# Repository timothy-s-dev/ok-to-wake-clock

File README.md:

# OK-to-Wake Clock - ESP32 Multi-Function Clock

This project provides code for a digital OK-to-Wake clock using an ESP32 with
multiple input and output components. The clock includes rotary encoder input
(w/ switch), RGB LED state indicator, alphanumeric display, and an RTC with
battery backup so the time is not lost when power is.

A schedule can be set for each day of the week, with the following time windows:

* Wind Down (Blue)
* Sleep (Red)
* Quiet (Yellow)
* Wake (White)

Depending on which window the current time falls in for the current day's
schedule the RGB LED will change colors.

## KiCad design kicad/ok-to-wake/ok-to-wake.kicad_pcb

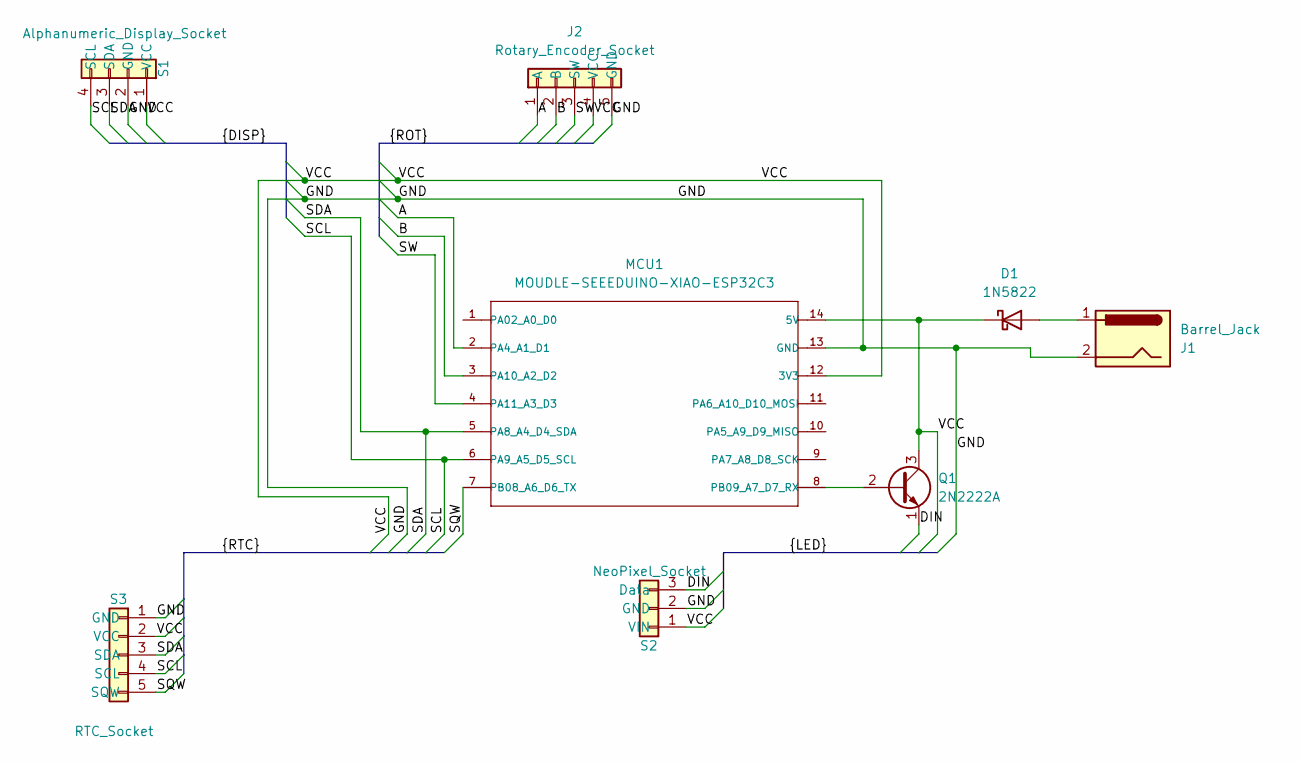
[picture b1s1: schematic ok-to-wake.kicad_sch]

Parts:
D1: 1N5822; D_DO-201AD_P15.24mm_Horizontal
J1: Barrel_Jack; JST_XH_B2B-XH-A_1x02_P2.50mm_Vertical
J2: Rotary_Encoder_Socket; JST_XH_B5B-XH-AM_1x05_P2.50mm_Vertical
MCU1: MOUDLE-SEEEDUINO-XIAO-ESP32C3; MCU_Seeed_ESP32C3
Q1: 2N2222A; TO-92
S1: Alphanumeric_Display_Socket; JST_XH_B4B-XH-AM_1x04_P2.50mm_Vertical
S2: NeoPixel_Socket; JST_XH_B3B-XH-AM_1x03_P2.50mm_Vertical
S3: RTC_Socket; PinHeader_1x05_P2.54mm_Vertical

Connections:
/A: J2.1 (A), MCU1.2 (PA4_A1_D1)
/B: J2.2 (B), MCU1.3 (PA10_A2_D2)
/DIN: Q1.1 (E), S2.3 (Data)
/GND: J1.2, J2.5 (GND), MCU1.13 (GND), S1.2 (GND), S2.2 (GND), S3.1 (GND)
/SCL: MCU1.6 (PA9_A5_D5_SCL), S1.4 (SCL), S3.4 (SCL)
/SDA: MCU1.5 (PA8_A4_D4_SDA), S1.3 (SDA), S3.3 (SDA)
/SQW: MCU1.7 (PB08_A6_D6_TX), S3.5 (SQW)
/SW: J2.3 (SW), MCU1.4 (PA11_A3_D3)
/VCC: D1.1 (K), J2.4 (VCC), MCU1.12 (3V3), MCU1.14 (5V), Q1.3 (C), S1.1 (VCC), S2.1 (VIN), S3.2 (VCC)
unnamed: D1.2 (A), J1.1
unnamed: MCU1.8 (PB09_A7_D7_RX), Q1.2 (B)

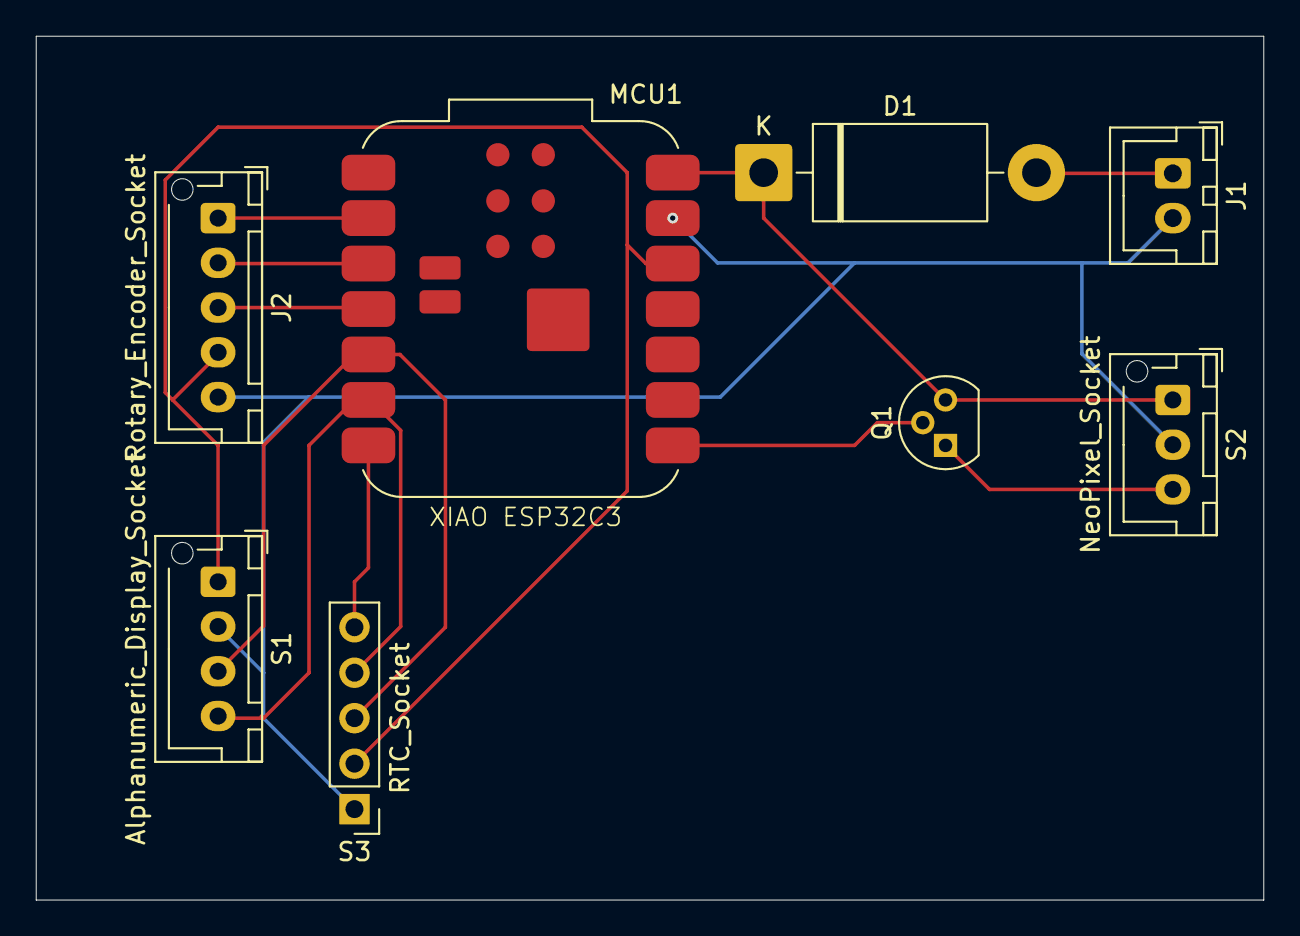
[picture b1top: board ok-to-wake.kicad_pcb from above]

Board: 2 copper layers, 68.6 x 48.3 mm, 8 parts (0 on the bottom side), 11 nets.

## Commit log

2025-07-07 Initial commit.
2025-07-07 Clean up readme
2025-07-09 Add date-reading functionality to the clock
2025-07-11 Add nap functionality
2025-07-11 Add schedule class and clean up
2025-07-12 First pass at lock functionality
2025-07-26 Add kicad files
2025-07-26 Switch to Seeed XIAO ESP32S3 and Adafruit NeoPixel
2025-07-26 Refactor state machine to split individual state logic to separate files
2025-07-26 Fix schedule reading bug (hours/minutes swapped)
2025-07-26 Add "Back" menu option
2025-07-27 Add brightness settings.
